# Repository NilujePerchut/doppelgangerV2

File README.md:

# Doppelganger V2 RevA0

## Requirements:

### Hardware:
* Kicad 5+
* python3
* skidl

### Software:

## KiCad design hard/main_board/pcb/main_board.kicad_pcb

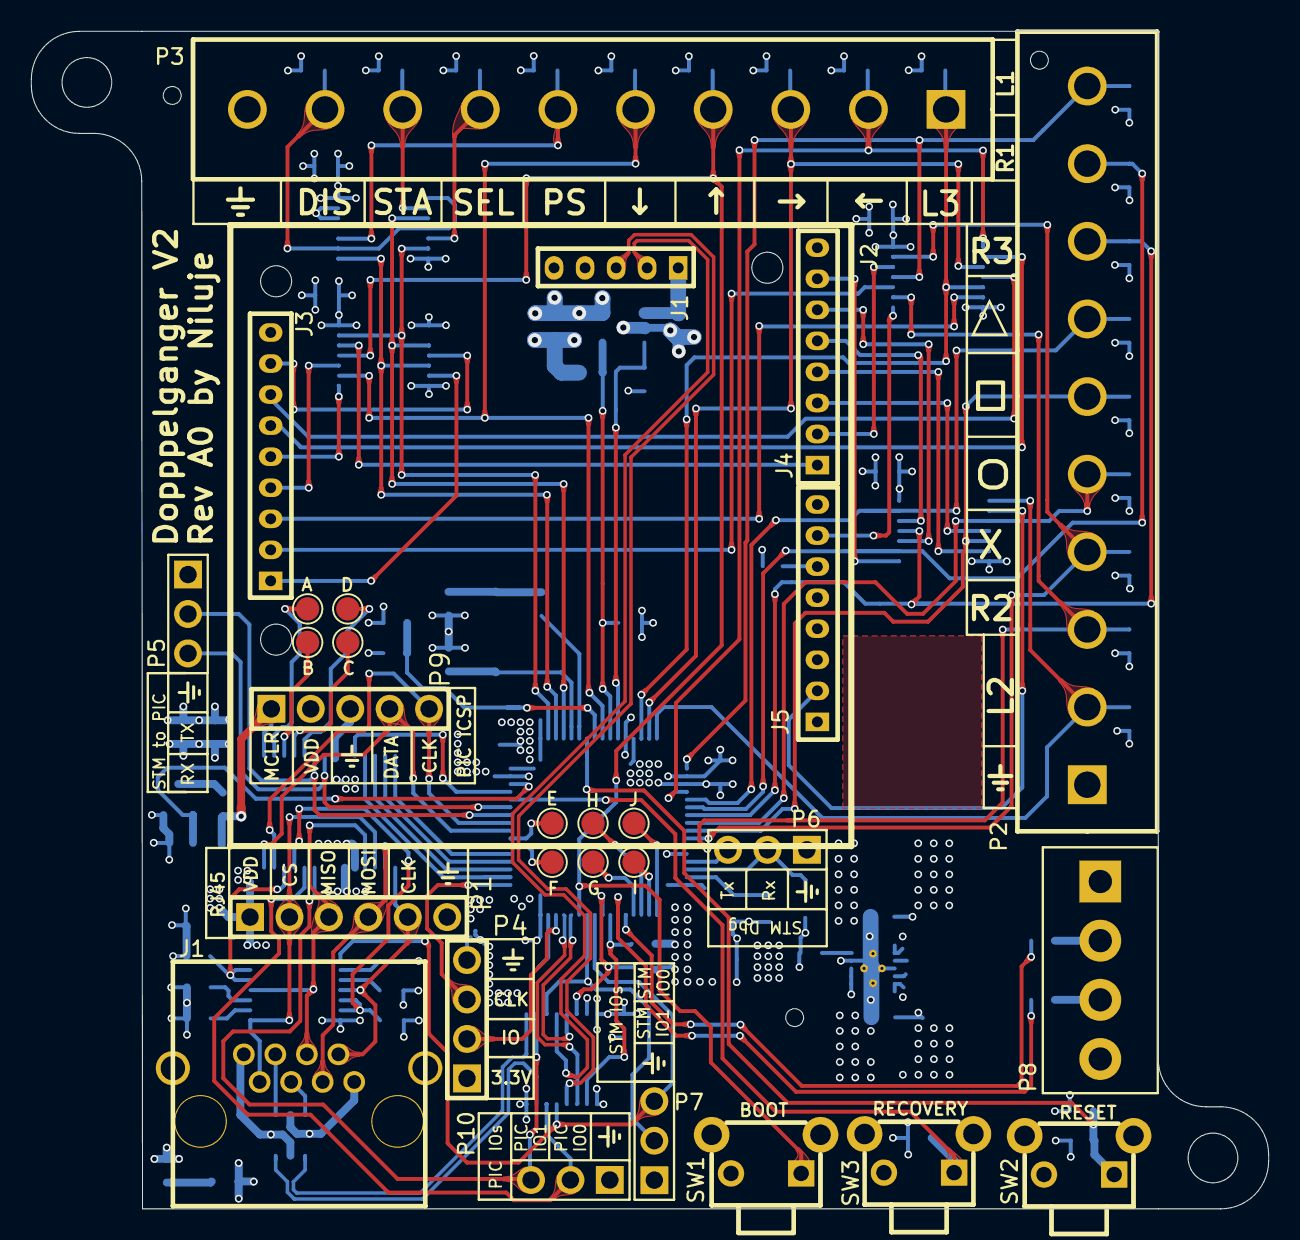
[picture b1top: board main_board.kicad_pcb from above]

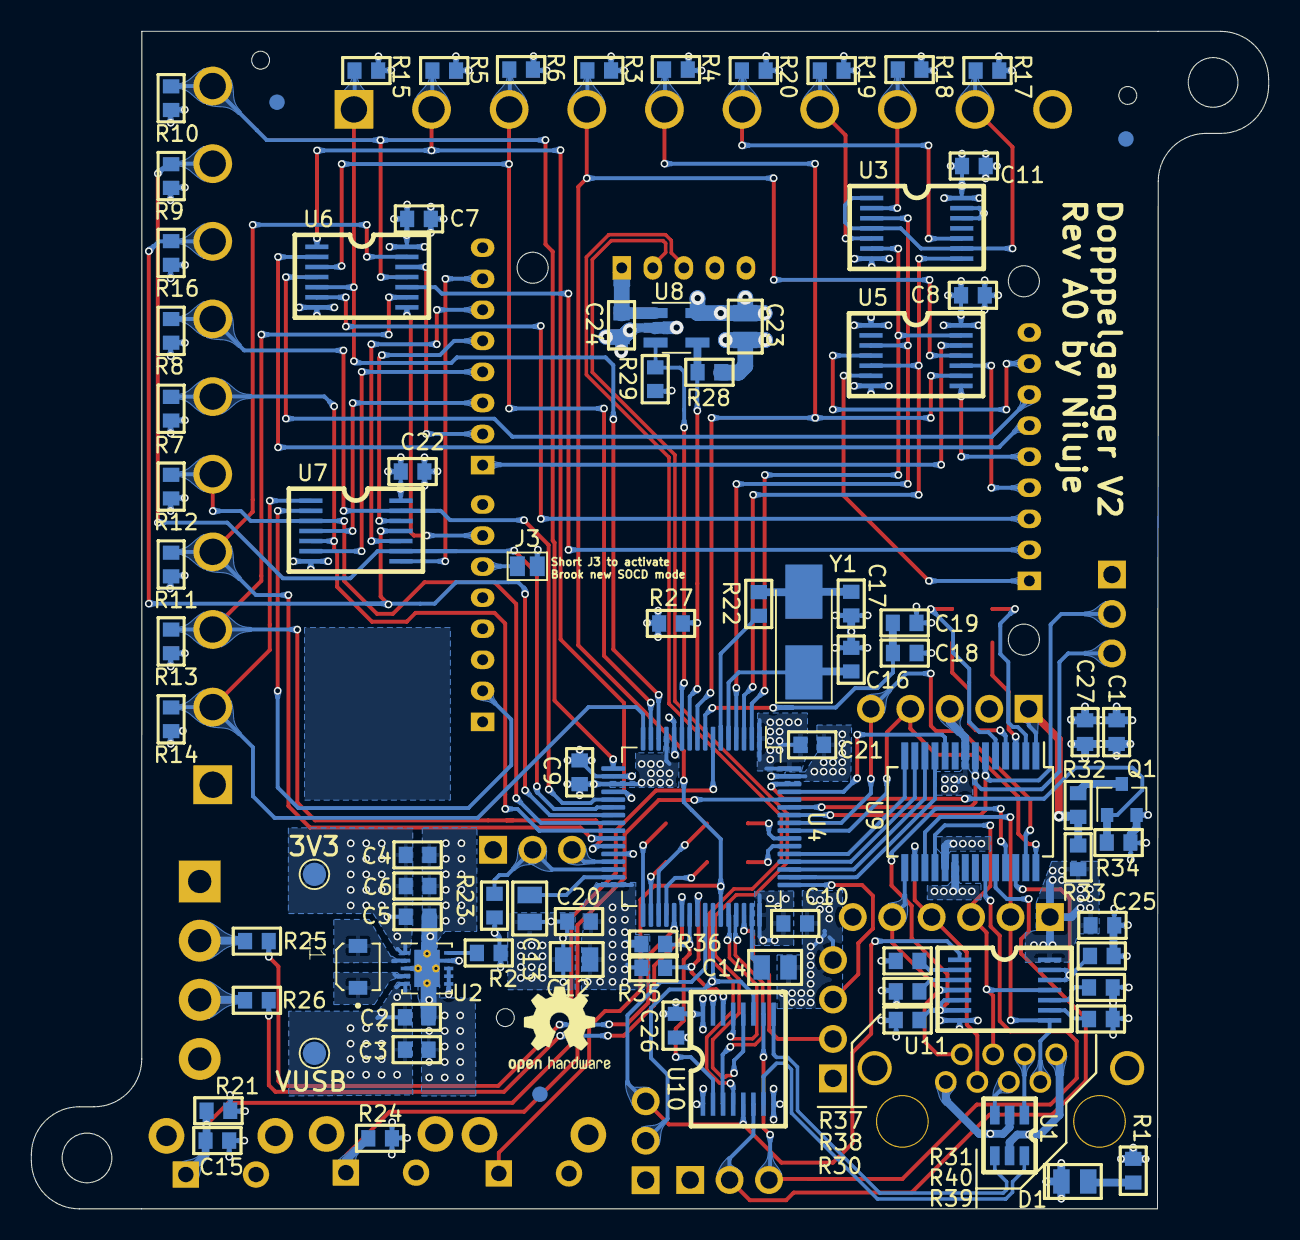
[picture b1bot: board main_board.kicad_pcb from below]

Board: 4 copper layers, 79.7 x 75.8 mm, 120 parts (89 on the bottom side), 111 nets.

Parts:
C1, C7, C8, C9, C10, C11, C15, C20, C21, C22, C24, C25, C26, C27: 100nF; 0603C
C2, C3, C4, C5, C6: 10uF; 0603C
C12: 4.7uF; 0805C
C13, C14: 2.2uF; 0805C
C16, C17: 30pF; 0603C
C18, C19: 10K; 0603C
C23: 1uF; 0805C
D1: LED; 0805LED
F1, F2: Fix; FIX
F3, F4, F5: Fix; JLCPCB_TOOLING_HOLE
FID1, FID2, FID3: FIDUCIAL
J1: RJ45
J2: BROOK_FB
J3: GS2
L1: L; 1227AS-H-1R5N=P2
P1: CONN_01X06; SIL6
P2, P3: BORNIER_10
P4: CONN_01X04; SIL4
P5, P6, P7, P10: CONN_01X03; SIL3
P8: CONN_01X04; Bornier4_3.81mm
P9: CONN_01X05; SIL5
Q1: Q_NMOS_DGS; SOT23
R1: 120.0; 0603R
R2, R22: 0R; 0603R
R3, R4, R5, R6, R7, R8, R9, R10, R11, R12, R13, R14, R15, R16, R17, R18, R19, R20, R21, R23, R27, R28, R29, R34, R35, R36: 10K; 0603R
R24: 100K; 0603R
R25, R26, R30, R31: 330R; 0603R
R32: 100R; 0603R
R33: 12K5; 0603R
R37, R40: 4K7; 0603R
R38, R39: 3K6; 0603R
S1, S2: Sakura; Sakura_solder_mask
SW1, SW2, SW3: SW_PUSH; BP
TP1, TP2, TP3, TP4, TP5, TP6, TP7, TP8, TP9, TP10, TP11, TP12: TestPoint; TestPoint_Pad_D1.5mm
U1: USBLC6-2SC6; TSOT-23-6
U2: TPS63000; Texas_DRC0010J_ThermalVias
U3: 74HC32; TSSOP14
U4: STM32F405RGTx; LQFP-64_10x10mm_P0.5mm
U5, U6, U7: 74LVC07; TSSOP14
U8: USBPowerSwitch; SOT23-5
U9: 16F18855; SSOP-28_5.3x10.2mm_P0.65mm
U10: SN74CBT3253; TSSOP16
U11: 74HC4066; TSSOP14
Y1: Crystal; Crystal_SMD_5032-2Pin_5.0x3.2mm_HandSoldering

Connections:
BOOT0: R24.1, SW3.1, U4.60
BROOK_POWER_CMD: R27.2, R28.2, U4.10, U8.4
BROOK_POWER_FAULTN: R29.2, U4.11, U8.3
BROOK_USB_N: J2.J1_2, U10.12
BROOK_USB_P: J2.J1_3, U10.4
CIRCLE: P2.5, R12.2, U4.24, U7.3
CIRCLE_BROOK: J2.J4_3, U7.4
CROSS: P2.4, R11.2, U4.26, U6.13
CROSS_BROOK: J2.J4_2, U6.12
DBG_RX: P6.2, R23.2, U4.30
DBG_TX: P6.3, U4.29
DISABLE: P3.9, R17.2, U3.1, U3.4, U3.9
DOWN: P3.5, R4.2, U4.9, U5.9
DOWN_BROOK: J2.J3_5, U5.8
GND: C1.2, C2.2, C3.2, C4.2, C5.2, C6.2, C7.2, C8.2, C9.2, C10.2, C11.2, C12.2, C13.2, C14.2, C15.2, C16.2, C17.2, C19.2, C20.2, C21.2, C22.2, C23.2, C24.2, C25.2, C26.2, C27.2, D1.K, J1.1, J2.J1_4, J2.J1_5, J2.J3_9, J2.J4_8, J2.J5_8, J3.2, P1.6, P2.1, P3.10, P4.4, P5.1, P6.1, P7.1, P8.4, P9.3, P10.1, Q1.2, R24.2, R28.1, R30.1, R31.1, R34.1, SW1.2, SW2.2, U1.2, U2.3, U2.9, U2.11, U3.7, U3.12, U3.13, U4.12, U4.18, U4.28, U4.63, U5.7, U6.7, U7.7, U8.2, U9.8, U9.19, U10.1, U10.8, U10.15, U11.7
GPIO0_UPPER_TERM_SW: R37.2, U11.2
HOME: P3.6, R20.2, U3.10
HOME_BROOK: J2.J3_1, U5.6
HOME_FILTERED: U3.8, U4.3, U5.5
L1: P2.10, R10.2, U4.17, U6.11
L1_BROOK: J2.J3_2, U6.10
L2: P2.2, R14.2, U4.16, U7.1
L2_BROOK: J2.J5_2, U7.2
L3: P3.1, R15.2, U4.14, U6.5
L3_BROOK: J2.J3_3, U6.6
LED_L: R25.1, U4.37
LED_R: R26.1, U4.38
LEFT: P3.2, R5.2, U4.20, U6.1
LEFT_BROOK: J2.J3_6, U6.2
MCLR: P9.1, R32.2, R33.2, U9.1
unnamed: D1.A, R1.2
unnamed: J1.5, U1.3
unnamed: J1.6, U1.1
unnamed: R2.2, U2.10
unnamed: L1.1, U2.4
unnamed: L1.2, U2.2
unnamed: C13.1, U4.31
unnamed: C14.1, U4.47
unnamed: C17.1, R22.2, Y1.2
unnamed: P8.2, R25.2
unnamed: P8.3, R26.2
unnamed: C18.2, C19.1, U4.8
unnamed: TP3.1, U4.55
unnamed: TP4.1, U4.33
unnamed: TP5.1, U4.34
unnamed: TP6.1, U4.35
unnamed: TP7.1, U4.36
unnamed: TP8.1, U4.54
unnamed: J2.J5_6, J3.1
unnamed: Q1.3, R32.1
unnamed: TP9.1, U9.2
unnamed: TP10.1, U9.3
unnamed: TP11.1, U9.4
unnamed: TP12.1, U9.5
R1: P2.9, R9.2, U4.22, U7.9
R1_BROOK: J2.J4_7, U7.8
R2: P2.3, R13.2, U4.27, U6.9
R2_BROOK: J2.J5_7, U6.8
R3: P2.8, R16.2, U4.23, U7.11
R3_BROOK: J2.J4_6, U7.10
RIGHT: P3.3, R6.2, U4.15, U6.3
RIGHT_BROOK: J2.J3_7, U6.4
RJ45_USB_N: U1.4, U10.9
RJ45_USB_P: U1.6, U10.7
RJ_SPI_CLK: J1.2, P1.5, U9.15, U11.4
RJ_SPI_CLK_UPPER_TERM_SW: R38.2, U11.3
RJ_SPI_CS: J1.7, P1.2, U9.17, U11.8
RJ_SPI_CS_UPPER_TERM_SW: R39.2, U11.9
RJ_SPI_MISO: J1.4, P1.3, U9.18, U11.11
RJ_SPI_MISO_UPPER_TERM_SW: R40.2, U11.10
RJ_SPI_MOSI: J1.3, P1.4, U9.16
SELECT: P3.7, R19.2, U3.5
SELECT_BROOK: J2.J4_1, U5.12
SELECT_FILTERED: U3.6, U4.2, U5.13
SQUARE: P2.6, R7.2, U4.25, U7.5
SQUARE_BROOK: J2.J4_4, U7.6
START: P3.8, R18.2, U3.2
START_BROOK: J2.J3_8, U5.4
START_FILTERED: U3.3, U4.4, U5.3
STM32_RESETn: C15.1, R21.2, SW2.1, U4.7
STM32_USB_N: U4.44, U10.13
STM32_USB_P: U4.45, U10.3
STM_TO_PIC_BOOT_CMD: U4.61, U9.10
STM_TO_PIC_DATA0: U4.50, U9.11
STM_TO_PIC_DATA1: U4.51, U9.12
STM_TO_PIC_DATA2: U4.52, U9.13
STM_TO_PIC_DATA3: U4.53, U9.14
STM_TO_PIC_ICSP_CLOCK: P9.5, U4.57, U9.27
STM_TO_PIC_ICSP_DATA: P9.4, U4.56, U9.28
STM_TO_PIC_RESET: Q1.1, R34.2, U4.62
STM_TO_PIC_UART_RX: P5.3, U4.59, U9.7
STM_TO_PIC_UART_TX: P5.2, U4.58, U9.6
SWDCLK: P4.3, U4.49
SWDIO: P4.2, U4.46
TRIANGLE: P2.7, R8.2, U4.21, U7.13
TRIANGLE_BROOK: J2.J4_5, U7.12
UP: P3.4, R3.2, SW1.1, U4.43, U5.11
UP_BROOK: J2.J3_4, U5.10
V5_SW: C24.1, J2.J1_1, U8.1
V33: C4.1, C5.1, C6.1, C7.1, C8.1, C9.1, C10.1, C11.1, C12.1, C20.1, C21.1, C22.1, C26.1, P4.1, P8.1, R2.1, R3.1, R4.1, R5.1, R6.1, R7.1, R8.1, R9.1, R10.1, R11.1, R12.1, R13.1, R14.1, R15.1, R16.1, R17.1, R18.1, R19.1, R20.1, R21.1, R23.1, R27.1, R35.1, R36.1, R37.1, SW3.2, TP2.1, U2.1, U3.14, U4.1, U4.13, U4.19, U4.32, U4.48, U4.64, U5.1, U5.14, U6.14, U7.14, U10.16
VUSB: C1.1, C2.1, C3.1, C18.1, C23.1, C25.1, C27.1, J1.8, P1.1, P9.2, R1.1, R29.1, R33.1, R38.1, R39.1, R40.1, TP1.1, U1.5, U2.5, U2.6, U2.7, U2.8, U8.5, U9.20, U11.14
XTAL_IN: C16.1, U4.5, Y1.1
XTAL_OUT: R22.1, U4.6
mux_sel0: R35.2, U4.40, U10.14
mux_sel1: R36.2, U4.39, U10.2
pic16_gpio0: P10.2, U9.24, U10.6
pic16_gpio1: P10.3, U9.23, U10.10
psx_term_cmd: R31.2, U9.26, U11.12, U11.13
snes_term_cmd: R30.2, U9.25, U11.5, U11.6
stm32_gpio0: P7.3, U4.41, U10.5, U11.1
stm32_gpio1: P7.2, U4.42, U10.11

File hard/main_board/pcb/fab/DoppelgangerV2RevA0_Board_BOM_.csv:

Designator,Comment,Footprint,LCSC part#
U1,USBLC6-2SC6,TSOT-23-6,C558442
C1,100nF,0603C,C14663
U2,TPS63000,Texas_DRC0010J_ThermalVias,C28060
L1,L,1227AS-H-1R5N=P2,C435389
R2,0R,0603R,C21189
C2,10uF,0603C,C19702
C3,10uF,0603C,C19702
C4,10uF,0603C,C19702
C5,10uF,0603C,C19702
C6,10uF,0603C,C19702
R3,10K,0603R,C25804
R4,10K,0603R,C25804
R5,10K,0603R,C25804
R6,10K,0603R,C25804
R7,10K,0603R,C25804
R8,10K,0603R,C25804
R9,10K,0603R,C25804
R10,10K,0603R,C25804
R11,10K,0603R,C25804
R12,10K,0603R,C25804
R13,10K,0603R,C25804
R14,10K,0603R,C25804
R15,10K,0603R,C25804
R16,10K,0603R,C25804
R17,10K,0603R,C25804
R18,10K,0603R,C25804
R19,10K,0603R,C25804
R20,10K,0603R,C25804
U3,74HC32,TSSOP14,C6087
C7,100nF,0603C,C14663
U4,STM32F405RGTx,LQFP-64_10x10mm_P0.5mm,C15742
Y1,Crystal,Crystal_SMD_5032-2Pin_5.0x3.2mm_HandSoldering,C115962
C8,100nF,0603C,C14663
C9,100nF,0603C,C14663
C10,100nF,0603C,C14663
C11,100nF,0603C,C14663
C12,4.7uF,0805C,C1779
C13,2.2uF,0805C,C49217
C14,2.2uF,0805C,C49217
R21,10K,0603R,C25804
C15,100nF,0603C,C14663
C16,30pF,0603C,C22397
R22,0R,0603R,C21189
C17,30pF,0603C,C22397
R23,10K,0603R,C25804
R24,100K,0603R,C25803
R25,330R,0603R,C23138
R26,330R,0603R,C23138
R27,10K,0603R,C25804
C18,10K,0603C,C25804
C19,10K,0603C,C25804
U5,74LVC07,TSSOP14,C6051
C20,100nF,0603C,C14663
U6,74LVC07,TSSOP14,C6051
C21,100nF,0603C,C14663
U7,74LVC07,TSSOP14,C6051
C22,100nF,0603C,C14663
U8,USBPowerSwitch,SOT23-5,C351147
C23,1uF,0805C,C28323
C24,100nF,0603C,C14663
R28,10K,0603R,C25804
R29,10K,0603R,C25804
U9,16F18855,SSOP-28_5.3x10.2mm_P0.65mm,C510915
C25,100nF,0603C,C14663
R30,330R,0603R,C23138
R31,330R,0603R,C23138
Q1,Q_NMOS_DGS,SOT23,C520561
R32,100R,0603R,C22775
R33,12K5,0603R,C22797
R34,10K,0603R,C23138
U10,SN74CBT3253,TSSOP16,C424399
C26,100nF,0603C,C14663
R35,10K,0603R,C25804
R36,10K,0603R,C25804
U11,74HC4066,TSSOP14,C5350
C27,100nF,0603C,C14663
R37,4K7,0603R,C23162
R38,3K6,0603R,C22980
R39,3K6,0603R,C22980
R40,4K7,0603R,C23162

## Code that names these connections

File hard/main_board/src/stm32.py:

#! /usr/bin/env python3
# -*- coding: utf-8 -*-

from skidl import Net
from lib.sch_utils import dop_part, bypass_cap, get_capa, get_res, pull_updown


def stm32(vin, gnd, switches, vio):
    """Set up the power stage."""

    sw_map = {"UP": "PA10",
              "DOWN": "PC1",
              "LEFT": "PA4",
              "RIGHT": "PA1",
              "SQUARE": "PC5",
              "TRIANGLE": "PA5",
              "R1": "PA6",
              "L1": "PA3",
              "CROSS": "PB0",
              "CIRCLE": "PC4",
              "R2": "PB1",
              "L2": "PA2",
              "L3": "PA0",
              "R3": "PA7",
              "START": "PC15",
              "SELECT": "PC13",
              "HOME": "PC14",
              }

    pic_iface = {"reset": Net("STM_TO_PIC_RESET"),
                 "icsp_clock": Net("STM_TO_PIC_ICSP_CLOCK"),
                 "icsp_data": Net("STM_TO_PIC_ICSP_DATA"),
                 "boot_cmd": Net("STM_TO_PIC_BOOT_CMD"),
                 # UART
                 "uart_tx": Net("STM_TO_PIC_UART_TX"),
                 "uart_rx": Net("STM_TO_PIC_UART_RX"),
                 # DATA[3:0]
                 "data0": Net("STM_TO_PIC_DATA0"),
                 "data1": Net("STM_TO_PIC_DATA1"),
                 "data2": Net("STM_TO_PIC_DATA2"),
                 "data3": Net("STM_TO_PIC_DATA3")}

    gpios = {"gpio0": Net("stm32_gpio0"),
             "gpio1": Net("stm32_gpio1")}

    usb = {"STM32_USB_P": Net("STM32_USB_P"),
           "STM32_USB_N": Net("STM32_USB_N")}

    mux_sel = {"mux_sel0": Net("mux_sel0"),
               "mux_sel1": Net("mux_sel1")}

    mcu = dop_part("STM32F405RGTX", "LQFP-64_10x10mm_P0.5mm",
                   fields={"Reference": "STM32F405RGT6",
                           "Descr": "ARM Cortex M4 ST version",
                           "CC": "2064363",
                           "JLCC": "C15742",
                           "JLROT": "90"})
    xtal = dop_part("Crystal", "Crystal_SMD_5032-2Pin_5.0x3.2mm_HandSoldering",
                    fields={"Reference": "QCL8.00000F18B23B",
                            "Descr": "Quartz 8MHz",
                            "CC": "2508448",
                            "JLCC": "C115962"})

    sw_conn = dop_part("CONN_01X04", "SIL4")
    pic_uart_conn = dop_part("CONN_01X03", "SIL3")
    serial_dbg_conn = dop_part("CONN_01X03", "SIL3")
    gpios_dbg_conn = dop_part("CONN_01X03", "SIL3")
    leds_conn = dop_part("CONN_01X04", "Bornier4_3.81mm")

    # Power
    mcu["VDD", "VDDA", "VBAT"] += vin
    mcu["VSS", "VSSA"] += gnd
    bypass_cap(vin, gnd, ["100nF"]*4, fields={"JLCC": "C14663"},
               descr="STM32F405")
    bypass_cap(vin, gnd, "4.7uF", package="0805", fields={"JLCC": "C1779"},
               descr="STM32F405")

    v_capas = [get_capa("2.2uF", "0805", fields={"JLCC": "C49217"})
               for i in range(2)]
    mcu["VCAP_1"] & v_capas[0][1, 2] & gnd
    mcu["VCAP_2"] & v_capas[1][1, 2] & gnd

    # Reset RC: 10K-100nF
    vin & get_res("10K", "0603", fields={"JLCC": "C25804"}) &\
        Net("STM32_RESETn") & mcu["NRST"] &\
        (get_capa("100nF", "0603", fields={"JLCC": "C14663"}) |\
         dop_part("SW_PUSH", "BP")) & gnd

    # XTAL
    # External capacitor value is given in ST AN2867: 2 (CL - CS)
    #     where CL is the crystal load capacitance
    #     where CS os the PCB capacitance (around 5-6pF)
    #     => 2 (20pF - 5pf) = 30pF
    mcu["PH0"] & Net("XTAL_IN") & xtal[1] &\
        get_capa("30pF", "0603", fields={"JLCC": "C22397"}) & gnd
    ext_res = get_res("0R", package="0603", fields={"JLCC": "C21189"})
    mcu["PH1"] & Net("XTAL_OUT") & ext_res[1, 2] & xtal[2] & \
        get_capa("30pF", "0603", fields={"JLCC": "C22397"}) & gnd

    # SWD interface
    sw_conn[1] += vin
    sw_conn[2] & Net("SWDIO") & mcu["PA13"]
    sw_conn[3] & Net("SWDCLK") & mcu["PA14"]
    sw_conn[4] += gnd

    # STM32 serial debug connector
    serial_dbg_conn[1] += gnd
    mcu["PB10"] & Net("DBG_TX") & serial_dbg_conn[3]
    dbg_rx = Net("DBG_RX")
    pull_updown(vin, dbg_rx, "10K", fields={"JLCC": "C25804"})
    mcu["PB11"] & dbg_rx & serial_dbg_conn[2]

    # PIC Interface
    mcu["PB6"] += pic_iface["uart_tx"]
    mcu["PB7"] += pic_iface["uart_rx"]
    mcu["PB5"] += pic_iface["icsp_clock"]
    mcu["PB4"] += pic_iface["icsp_data"]
    mcu["PB9"] += pic_iface["reset"]
    mcu["PB8"] += pic_iface["boot_cmd"]
    mcu["PA15"] += pic_iface["data0"]
    mcu["PC10"] += pic_iface["data1"]
    mcu["PC11"] += pic_iface["data2"]
    mcu["PC12"] += pic_iface["data3"]

    # Put PIC UART interface on a connector for debug purposes
    pic_uart_conn[1] += gnd
    pic_uart_conn[2] += pic_iface["uart_tx"]
    pic_uart_conn[3] += pic_iface["uart_rx"]

    # Buttons
    for bt_name in sw_map:
        mcu[sw_map[bt_name]] += switches[bt_name]

    # Gpios
    mcu["PA8"] & gpios_dbg_conn[3] & gpios["gpio0"]
    mcu["PA9"] & gpios_dbg_conn[2] & gpios["gpio1"]
    gpios_dbg_conn[1] += gnd

    # USB
    mcu["PA12"] += usb["STM32_USB_P"]
    mcu["PA11"] += usb["STM32_USB_N"]

    # BOOT signals
    boot0 = Net("BOOT0")
    mcu["BOOT0"] & boot0 & get_res("100K", package="0603",
                                   fields={"JLCC": "C25803"}) & gnd
    boot0 & dop_part("SW_PUSH", "BP") & vin

    mcu["PB2"] += gnd  # BOOT1

    # Leds
    leds_conn[1] += vin
    mcu["PC6"] & Net("LED_L") & get_res("330R", "0603",
                                        fields={"JLCC": "C23138"}) &\
                                        leds_conn[2]
    mcu["PC7"] & Net("LED_R") & get_res("330R", "0603",
                                        fields={"JLCC": "C23138"}) &\
                                        leds_conn[3]
    leds_conn[4] += gnd

    # Mux Selection
    mcu["PC9"] += mux_sel["mux_sel0"]
    mcu["PC8"] += mux_sel["mux_sel1"]

    # Brook power command
    brook_power_cmd = Net("BROOK_POWER_CMD")
    mcu["PC2"] += brook_power_cmd
    pull_updown(vin, brook_power_cmd, "10K", fields={"JLCC": "C25804"})
    # Also provide a signal that acts as a placeholder
    brook_power_switch_faultn = Net("BROOK_POWER_FAULTN")
    mcu["PC3"] += brook_power_switch_faultn

    # Vio analog (simple divider by 2)
    r_ana = [get_capa("10K", "0603", fields={"JLCC": "C25804"})
             for i in range(2)]
    vio & r_ana[0] & mcu["PC0"] & r_ana[1] & gnd

    # Not connected
    not_connected = ["PB3", "PB12", "PB13", "PB14", "PB15", "PD2"]
    for nc in not_connected:
        mcu[nc] & dop_part("TestPoint", "TestPoint_Pad_D1.5mm")

    return pic_iface, gpios, usb, mux_sel, brook_power_cmd,\
        brook_power_switch_faultn

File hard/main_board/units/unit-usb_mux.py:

#! /usr/bin/env python3
# -*- coding: utf-8 -*-

from skidl import Net, POWER
from src.usb_mux import usb_mux
from lib.sch_utils import unit_map_on_he10, run_unit


def unit_usb_mux():
    """Unit test the power stage"""
    # Input signals & connector
    power = {"vin": Net("vin"), "gnd": Net("gnd")}
    power["vin"].drive = POWER
    power["gnd"].drive = POWER

    sel = {name: Net(name) for name in ["mux_sel0", "mux_sel1"]}
    rj45 = {name: Net(name) for name in ["rj45_to_mux_0_usb_p",
                                         "rj45_to_mux_1_usb_n"]}
    pic = {"gpio0": Net("pic16_gpio0"), "gpio1": Net("pic16_gpio1")}
    stm = {"gpio0": Net("stm32_gpio0"), "gpio1": Net("stm32_gpio1")}
    stm_usb = {name: Net(name) for name in ["STM32_USB_P", "STM32_USB_N"]}
    brook_usb = {name: Net(name) for name in ["BROOK_USB_P", "BROOK_USB_N"]}

    # pic and stm have same keys, so they cannot be merged in nets
    nets = {**power, **sel, **rj45, **stm_usb, **brook_usb}
    nets_v = list(nets.values()) + list(pic.values()) + list(stm.values())
    unit_map_on_he10(nets_v)

    usb_mux(power["vin"], power["gnd"], sel, rj45, pic, stm, stm_usb, brook_usb,
            default_channel=2)

if __name__ == "__main__":
    run_unit(unit_usb_mux)

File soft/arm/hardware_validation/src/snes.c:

#include <libopencm3/stm32/rcc.h>
#include <libopencm3/stm32/gpio.h>
#include <libopencm3/stm32/usart.h>
#include "doppelganger.h"
#include "snes.h"
#include "clc.h"
#include "pic_iface.h"
#include "keys.h"


/* Quick and dirty snes test
 *
 * | RJ45 pin |  PU  | Function |    Signal   | PIC PORT | CLC channel |     dir     | ARM PORT | ARM DIR |
 * +----------+------+----------+-------------+----------+-------------+-------------+----------+---------+
 * | 2        | 3.5K | Clock    | RJ_SPI_CLK  |   RC4    | 1           | RJ45 -> ARM | GPIOA-15 | In      |
 * | 4        |      | Data     | RJ_SPI_MISO |   RC7    | 4           | ARM -> RJ45 | GPIOC-12 | Out     |
 * | 7        | 3.5K | Latch    | RJ_SPI_CS   |   RC6    | 3           | RJ45 -> ARM | GPIOC-11 | In      |
 * +----------+------+----------+-------------+----------+-------------+-------------+----------+---------+
 *
 */

extern volatile struct keys key_buff;

#define SNES_PORT GPIO15
#define SNES_SCK GPIO15

static inline unsigned char snes_sck(void)
{
	return gpio_get(GPIOA, GPIO15)?1:0;
}

static inline unsigned char snes_cs(void)
{
	return gpio_get(GPIOC, GPIO11)?1:0;
}

static inline void snes_do(int val)
{
	if (val)
		gpio_set(GPIOC, GPIO12);
	else
		gpio_clear(GPIOC, GPIO12);
}

void snes_init(void)
{
	rcc_periph_clock_enable(RCC_GPIOA);
	rcc_periph_clock_enable(RCC_GPIOC);

	/* Setup CLC */
	gpio_mode_setup(GPIOA, GPIO_MODE_INPUT, GPIO_PUPD_NONE, GPIO15); // Channel1
	gpio_mode_setup(GPIOC, GPIO_MODE_INPUT, GPIO_PUPD_NONE, GPIO11); // Channel3
	gpio_mode_setup(GPIOC, GPIO_MODE_OUTPUT, GPIO_PUPD_NONE, GPIO12); // Channel4
	setup_clc_passthrough_channel1(RJ45_2_ARM);
	setup_clc_passthrough_channel3(RJ45_2_ARM);
	setup_clc_passthrough_channel4(ARM_2_RJ45);

	/* Set pullups */
	usart_send_blocking(PIC_USART, 'P');

}

void snes(void)
{
	init_keys();
	snes_init();
	snes_do(1);
	while(1) {
		update_key_buff();

		/* Idle */
		snes_do(1);

		/* Wait for latch */
		while(!snes_cs());
		while(snes_cs());

		snes_do(key_buff.lk);
		while(snes_sck());
		while(!snes_sck());

		snes_do(key_buff.lp);
		while(snes_sck());
		while(!snes_sck());

		snes_do(key_buff.select);
		while(snes_sck());
		while(!snes_sck());

		snes_do(key_buff.start);
		while(snes_sck());
		while(!snes_sck());

		snes_do(key_buff.up);
		while(snes_sck());
		while(!snes_sck());

		snes_do(key_buff.down);
		while(snes_sck());
		while(!snes_sck());

		snes_do(key_buff.left);
		while(snes_sck());
		while(!snes_sck());

		snes_do(key_buff.right);
		while(snes_sck());
		while(!snes_sck());

		snes_do(key_buff.mk);
		while(snes_sck());
		while(!snes_sck());

		snes_do(key_buff.mp);
		while(snes_sck());
		while(!snes_sck());

		snes_do(key_buff.hp);
		while(snes_sck());
		while(!snes_sck());

		snes_do(key_buff.hk);
		while(snes_sck());
		while(!snes_sck());
		snes_do(1);
	}
}

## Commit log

2022-08-11 Initial commit with doc and README
2022-08-13 [HARD] Doppenganger V2 RevA0 PCB
2022-08-13 [SOFT] Add arm bootloader & black magic probe bins
2022-08-13 [SOFT] Add PIC first firmware
2022-08-13 [SOFT] Add arm soft part
2022-08-13 [SOFT] Updates main board hardware validation plan
2022-10-09 Main board hardware validation done
    SNES POC OK
2022-10-22 [SOFT] Create Doppelganger ARM app with keys subsystem
    Includes Unit tests (first version)
    Keys need to access the config
    Working Keys
